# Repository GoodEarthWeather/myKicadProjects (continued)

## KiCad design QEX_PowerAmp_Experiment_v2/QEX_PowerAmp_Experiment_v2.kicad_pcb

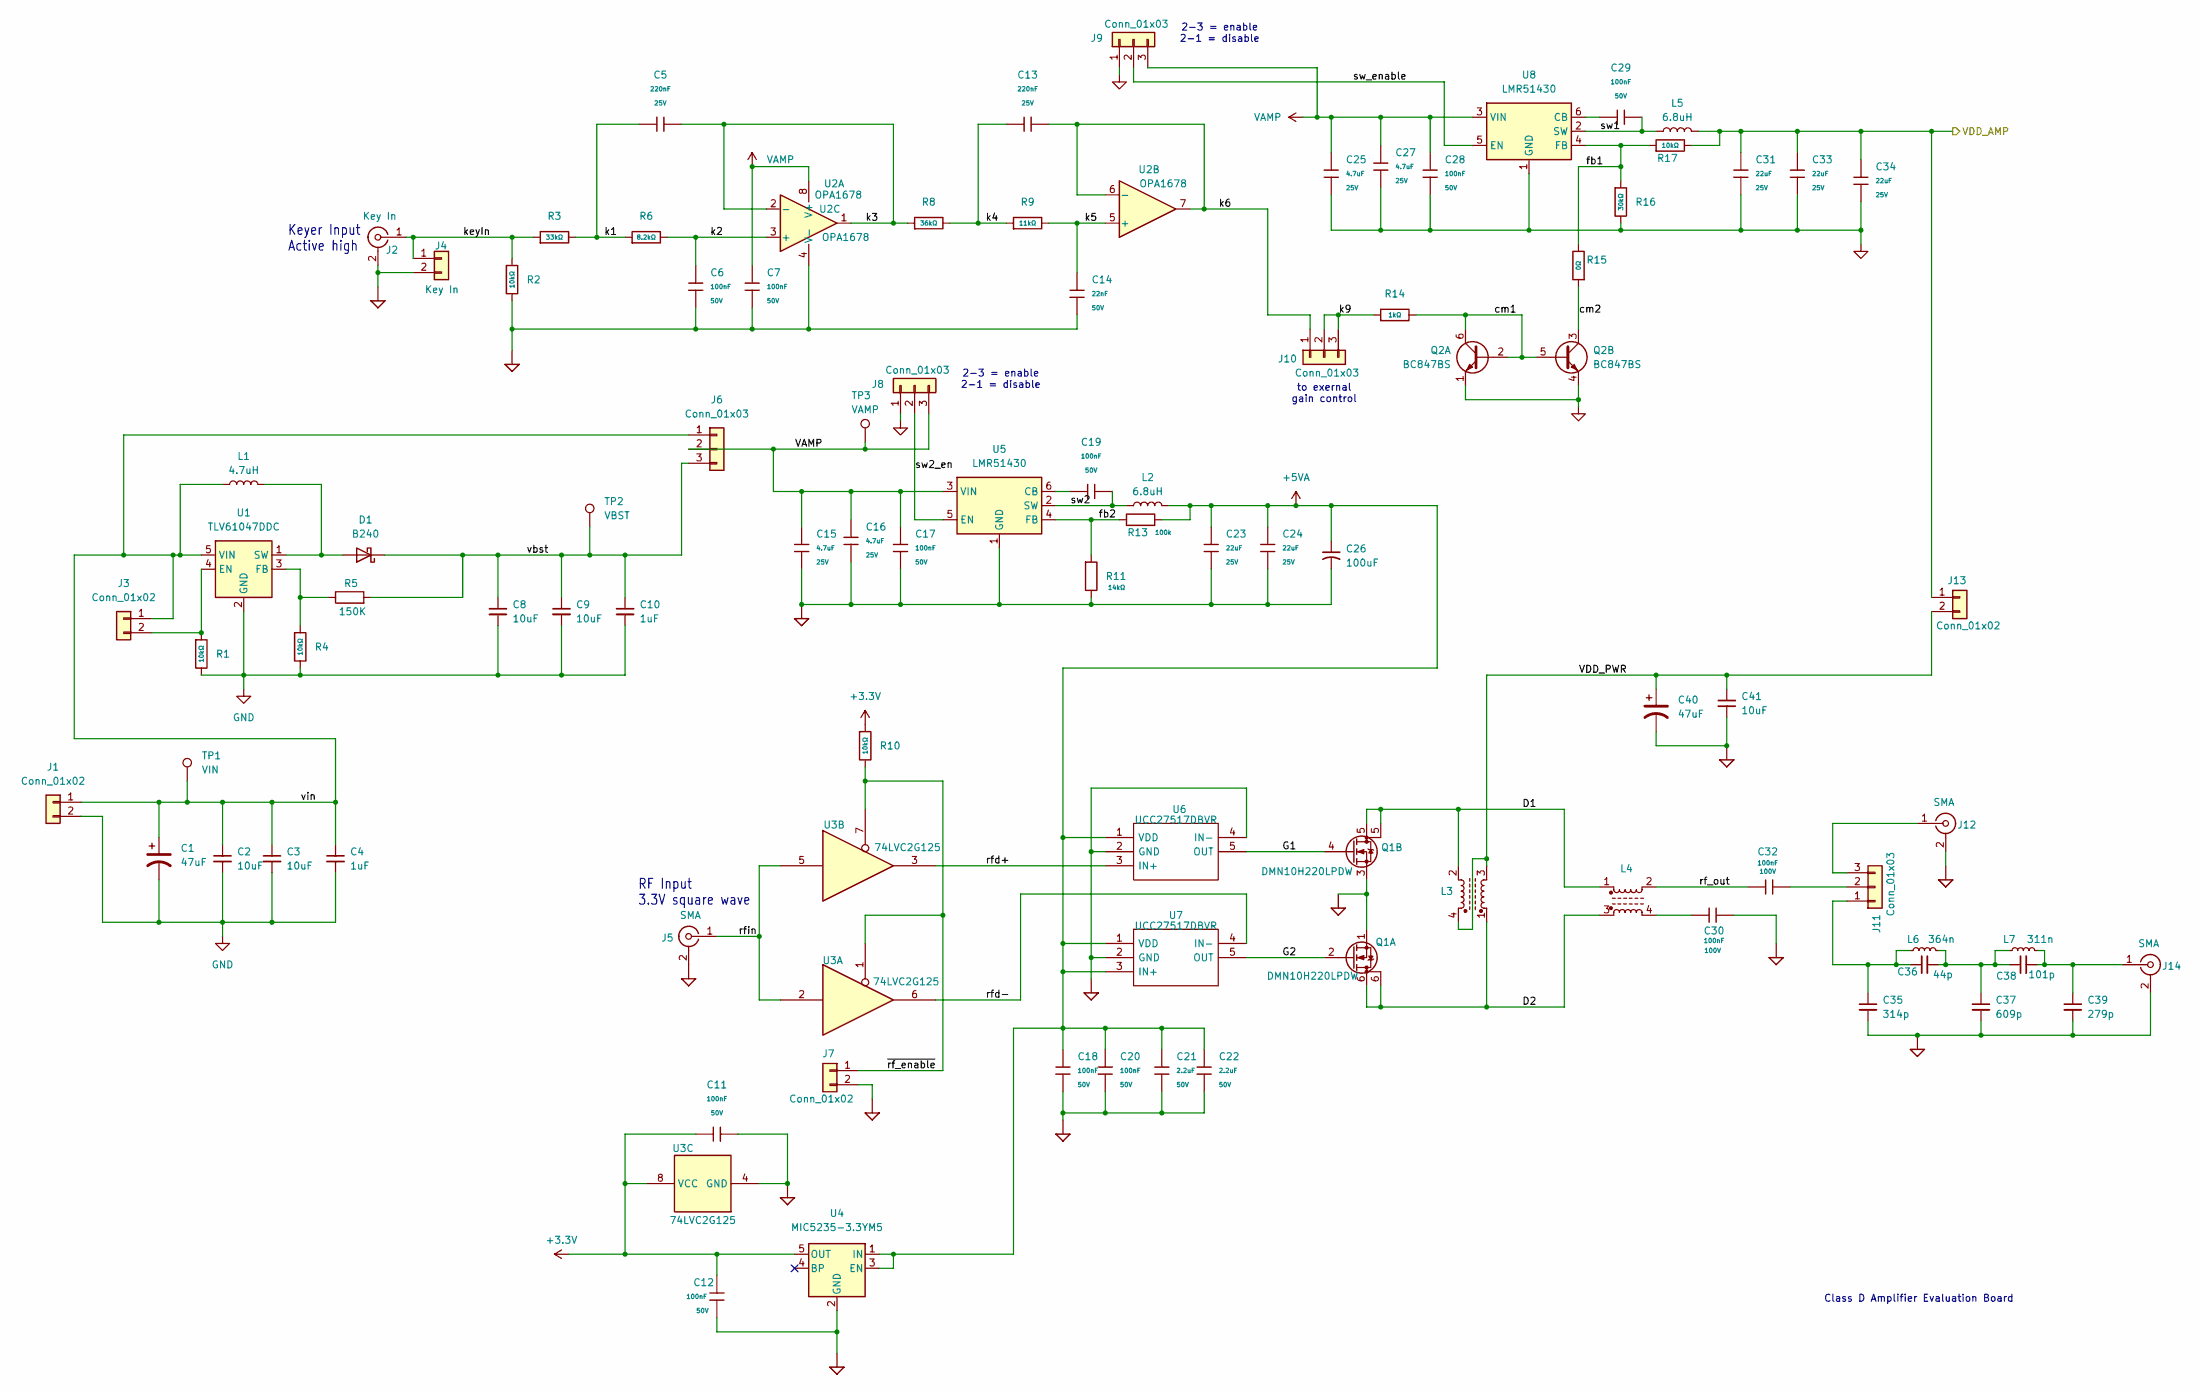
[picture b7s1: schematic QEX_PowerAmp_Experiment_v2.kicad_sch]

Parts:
C1, C40: 47uF; CP_Elec_6.3x5.8; MouserPN 667-EEE-FK1V470P
C2, C3, C8, C9, C41: 10uF; C_1206; MouserPN 810-CGA5L1X7R1H106K1
C4, C10: 1uF; C_0603; MouserPN 963-BASG168AB7105KT
C5, C13: 220nF; C_0603; Voltage Rated 25V; Tolerance ±10%; Part CL10B224KA8NNNC; LCSC C21120
C6, C7, C11, C12, C17, C18, C19, C20, C28, C29: 100nF; C_0603; Voltage Rated 50V; Tolerance ±10%; Part CC0603KRX7R9BB104; LCSC C14663
C14: 22nF; C_0603; Voltage Rated 50V; Tolerance ±10%; Part CL10B223KB8NNNC; LCSC C21122
C15, C16, C25, C27: 4.7uF; C_0805; Voltage Rated 25V; Tolerance ±10%; Part CL21A475KAQNNNE; LCSC C1779
C21, C22: 2.2uF; C_0805; Voltage Rated 50V; Tolerance ±10%; Part CL21A225KBQNNNE; LCSC C377773
C23, C24, C31, C33, C34: 22uF; C_0805; Voltage Rated 25V; Tolerance ±20%; Part CL21A226MAQNNNE; LCSC C45783
C26: 100uF; C_Elec_6.3x5.8; MouserPN 667-EEE-FT1V101AP
C30, C32: 100nF; C_0805; Voltage Rated 100V; Tolerance ±10%; Part CL21B104KCFNNNE; LCSC C28233
C35: 314p; C_1206_3216Metric_Pad1.33x1.80mm_HandSolder
C36: 44p; C_1206_3216Metric_Pad1.33x1.80mm_HandSolder
C37: 609p; C_1206_3216Metric_Pad1.33x1.80mm_HandSolder
C38: 101p; C_1206_3216Metric_Pad1.33x1.80mm_HandSolder
C39: 279p; C_1206_3216Metric_Pad1.33x1.80mm_HandSolder
D1: B240; D_SMB; MouserPN 625-B240A-E3
J1, J3, J7, J13: Conn_01x02; PinHeader_1x02_P2.54mm_Vertical
J2: Key In; SMA_Molex_73251-1153_EdgeMount_Horizontal
J4: Key In; PinHeader_1x02_P2.54mm_Vertical
J5, J12, J14: SMA; SMA_Molex_73251-1153_EdgeMount_Horizontal
J6, J8, J9, J10, J11: Conn_01x03; PinHeader_1x03_P2.54mm_Vertical
L1: 4.7uH; L_TechFuse_SL0420; LCSC C22463808
L2, L5: 6.8uH; L_TechFuse_SL0624; MouserPN 710-7447714068
L3, L4: L_Ferrite_Coupled; Transformer_Toroid_Horizontal_D14.0mm_Amidon-T50
L6: 364n; L_Toroid_Horizontal_D12.7mm_P20.00mm_Diameter14-5mm_Amidon-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
L7: 311n; L_Toroid_Horizontal_D12.7mm_P20.00mm_Diameter14-5mm_Amidon-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
Q1: DMN10H220LPDW; DMN10H220LPDW13; MouserPN 621-DMN10H220LPDW-13
Q2: BC847BS; SOT-363_SC-70-6; Part BC847BS; LCSC C41375126
R1, R2, R4, R10, R17: 10kΩ; R_0603; Overload Voltage (Max) 75V; Tolerance ±1%; Part 0603WAF1002T5E; LCSC C25804
R3: 33kΩ; R_0603; Overload Voltage (Max) 75V; Tolerance ±1%; Part 0603WAF3302T5E; LCSC C4216
R5: 150K; R_0603; JLCPCB C22807
R6: 8.2kΩ; R_0603; Overload Voltage (Max) 75V; Tolerance ±1%; Part 0603WAF8201T5E; LCSC C25981
R8: 36kΩ; R_0603; Overload Voltage (Max) 75V; Tolerance ±1%; Part 0603WAF3602T5E; LCSC C23147
R9: 11kΩ; R_0603; Overload Voltage (Max) 75V; Tolerance ±1%; Part 0603WAF1102T5E; LCSC C25950
R11: 14kΩ; R_0603; Overload Voltage (Max) 75V; Tolerance ±1%; Part 0603WAF3002T5E; LCSC C22984
R13: 100k; R_0603; Overload Voltage (Max) 75V; Tolerance ±1%; Part 0603WAF1002T5E; LCSC C25804
R14: 1kΩ; R_0603; Overload Voltage (Max) 75V; Tolerance ±1%; Part 0603WAF2701T5E; LCSC C21190
R15: 0Ω; R_0603; Overload Voltage (Max) 75V; Tolerance ±1%; Part 0603WAF0000T5E; LCSC C21189
R16: 30kΩ; R_0603; Overload Voltage (Max) 75V; Tolerance ±1%; Part 0603WAF3002T5E; LCSC C22984
TP1: VIN; TestPoint_Keystone_5000-5004_Miniature; MouserPN 534-5003
TP2: VBST; TestPoint_Keystone_5000-5004_Miniature; MouserPN 534-5003
TP3: VAMP; TestPoint_Keystone_5000-5004_Miniature; MouserPN 534-5003
U1: TLV61047DDC; SOT-23-5; MouserPN 595-TLV61047DDCR; JLCPCB C44538408
U2: OPA1678; SOIC-8_3.9x4.9mm_P1.27mm; JLCPCB C192421
U3: 74LVC2G125; SSOP-8_2.95x2.8mm_P0.65mm; MouserPN 595-74LVC2G125DCTRE4
U4: MIC5235-3.3YM5; SOT-23-5; MouserPN 998-MIC5235-3.3YM5TR
U5, U8: LMR51430; SOT-23-6; LCSC C5185863
U6, U7: UCC27517DBVR; SOT-23-5_HandSoldering; Mouser Part Number 595-UCC27517DBVR

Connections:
+3.3V: C11.1, C12.1, R10.1, U3.8 (VCC), U4.5 (OUT)
+5VA: C18.1, C20.1, C21.1, C22.1, C23.1, C24.1, C26.1, L2.2, R13.2, U4.1 (IN), U4.3 (EN), U6.1 (VDD), U7.1 (VDD), U7.3 (IN+)
/D1: L3.2, L4.1, Q1.5 (D)
/D2: L3.1, L4.3, Q1.6 (D)
/G1: Q1.4 (G), U6.5 (OUT)
/G2: Q1.2 (G), U7.5 (OUT)
/VDD_AMP: C31.1, C33.1, C34.1, J13.1, L5.2, R17.2
/VDD_PWR: C40.1, C41.1, J13.2, L3.3, L3.4
/cm1: Q2.2 (B1), Q2.5 (B2), Q2.6 (C1), R14.2
/cm2: Q2.3 (C2), R15.1
/fb1: R15.2, R16.1, R17.1, U8.4 (FB)
/fb2: R11.1, R13.1, U5.4 (FB)
/k1: C5.1, R3.2, R6.1
/k2: C6.1, R6.2, U2.3 (+)
/k3: C5.2, R8.1, U2.1, U2.2 (-)
/k4: C13.1, R8.2, R9.1
/k5: C14.1, R9.2, U2.5 (+)
/k6: C13.2, J10.1, U2.6 (-), U2.7
/k9: J10.2, J10.3, R14.1
/keyIn: J2.1 (In), J4.1, R2.1, R3.1
/rf_out: C32.1, L4.2
/rfd+: U3.3, U6.3 (IN+)
/rfd-: U3.6, U7.4 (IN-)
/rfin: J5.1 (In), U3.2, U3.5
/sw1: C29.2, L5.1, U8.2 (SW)
/sw2: C19.2, L2.1, U5.2 (SW)
/sw2_en: J8.2, U5.5 (EN)
/sw_enable: J9.2, U8.5 (EN)
/vbst: C8.1, C9.1, C10.1, D1.1 (K), J6.3, R5.2, TP2.1
/vin: C1.1, C2.1, C3.1, C4.1, J1.1, J3.1, J6.1, L1.1, TP1.1, U1.5 (VIN)
/~rf_enable: J7.1, R10.2, U3.1, U3.7
GND: C1.2, C2.2, C3.2, C4.2, C6.2, C7.2, C8.2, C9.2, C10.2, C11.2, C12.2, C14.2, C15.2, C16.2, C17.2, C18.2, C20.2, C21.2, C22.2, C23.2, C24.2, C25.2, C26.2, C27.2, C28.2, C30.2, C31.2, C33.2, C34.2, C35.2, C37.2, C39.2, C40.2, C41.2, J1.2, J2.2 (Ext), J4.2, J5.2 (Ext), J7.2, J8.1, J9.1, J12.2 (Ext), J14.2 (Ext), Q1.1 (S), Q1.3 (S), Q2.1 (E1), Q2.4 (E2), R1.2, R2.2, R4.2, R11.2, R16.2, U1.2 (GND), U2.4 (V-), U3.4 (GND), U4.2 (GND), U5.1 (GND), U6.2 (GND), U6.4 (IN-), U7.2 (GND), U8.1 (GND)
unnamed: C30.1, L4.4
unnamed: C36.2, C37.1, C38.1, L6.2, L7.1
unnamed: D1.2 (A), L1.2, U1.1 (SW)
unnamed: J3.2, R1.1, U1.4 (EN)
unnamed: C35.1, C36.1, J11.1, L6.1
unnamed: C32.2, J11.2
unnamed: J11.3, J12.1 (In)
unnamed: C38.2, C39.1, J14.1 (In), L7.2
unnamed: R4.1, R5.1, U1.3 (FB)
unnamed: C19.1, U5.6 (CB)
unnamed: C29.1, U8.6 (CB)
VAMP: C7.1, C15.1, C16.1, C17.1, C25.1, C27.1, C28.1, J6.2, J8.3, J9.3, TP3.1, U2.8 (V+), U5.3 (VIN), U8.3 (VIN)

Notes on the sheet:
to exernal gain control
Class D Amplifier Evaluation Board
RF Input 3.3V square wave
2-3 = enable 2-1 = disable
Keyer Input Active high

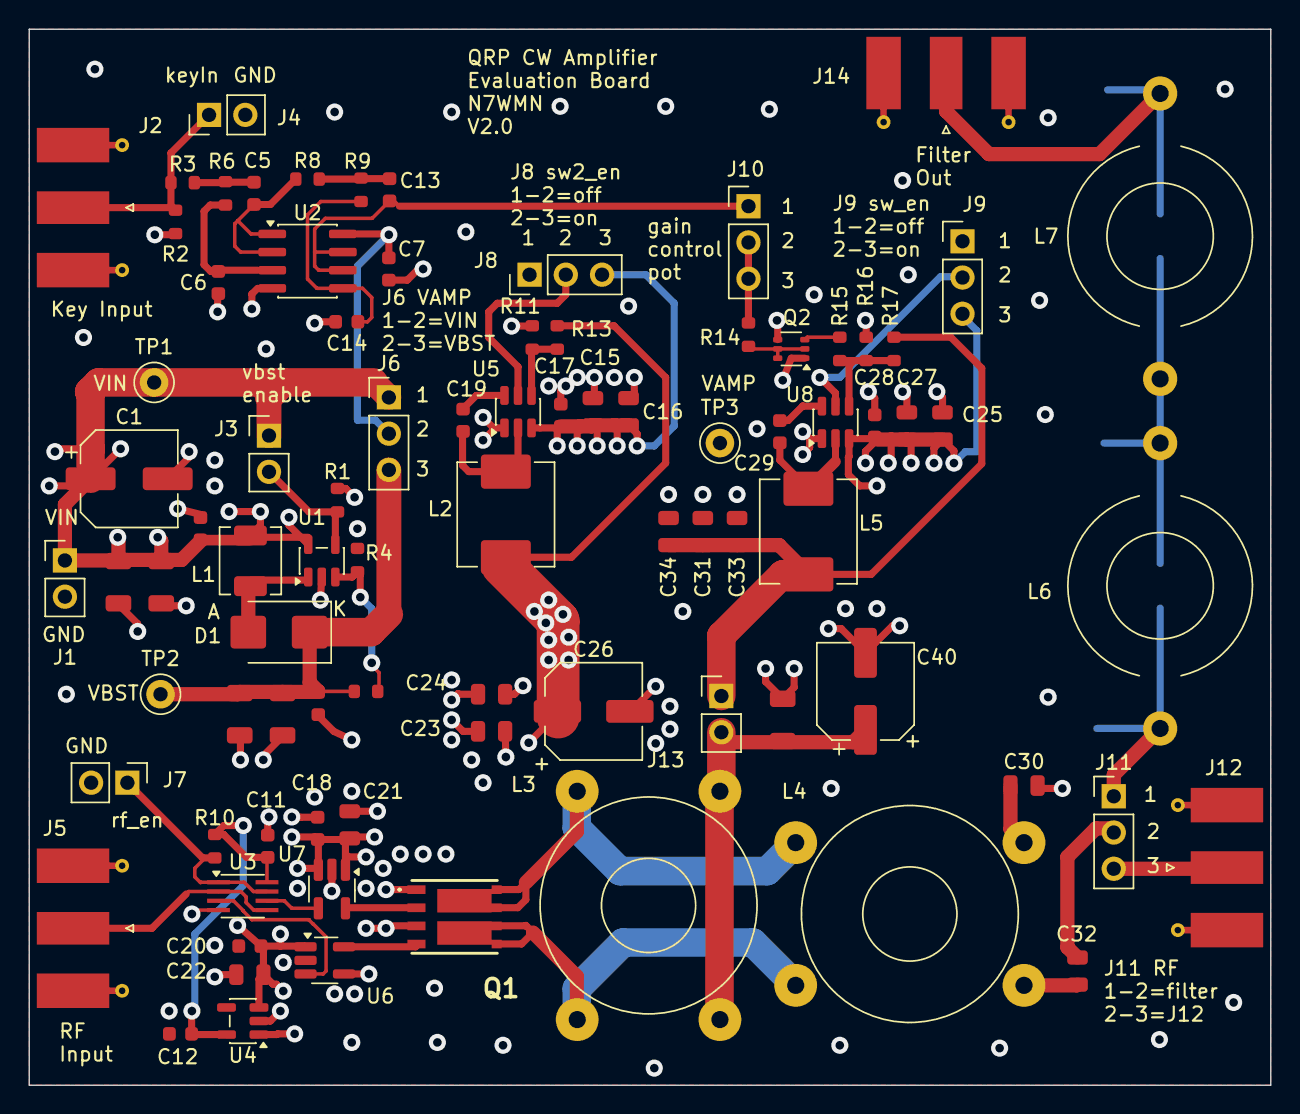
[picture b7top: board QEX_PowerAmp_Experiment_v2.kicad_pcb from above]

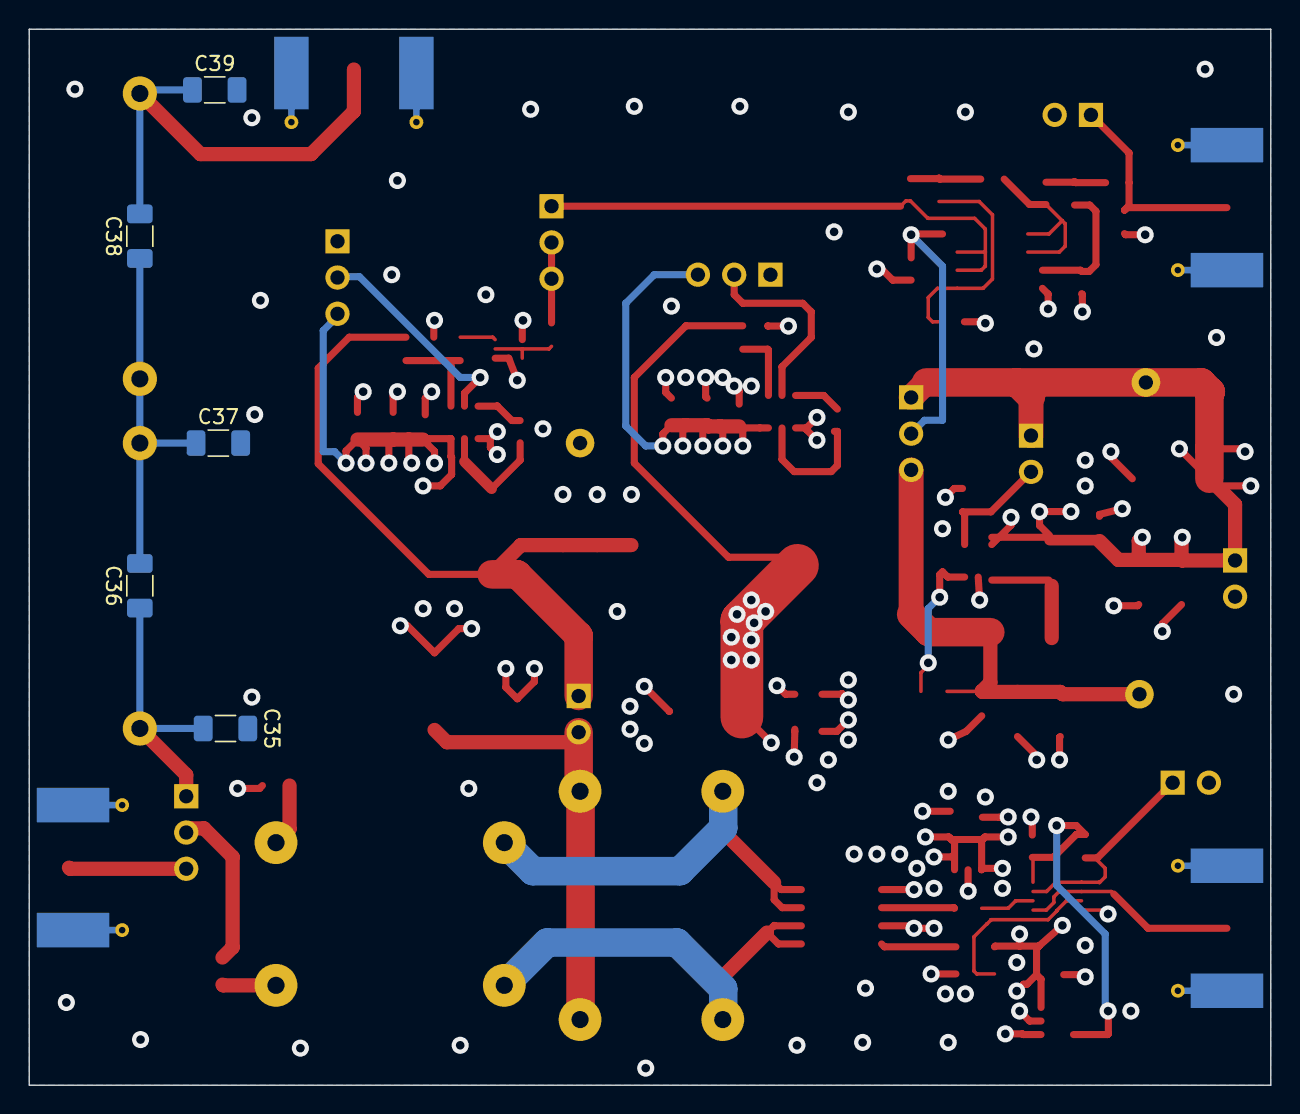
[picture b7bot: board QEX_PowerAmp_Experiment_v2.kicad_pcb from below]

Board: 4 copper layers, 87.0 x 74.0 mm, 91 parts (5 on the bottom side), 44 nets.

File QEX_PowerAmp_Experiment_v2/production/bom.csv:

Designator,Footprint,Comment,LCSC Part #
"C1, C40",CP_Elec_6.3x5.8,47uF,C336786
"C10, C4",C_0603,1uF,C15849
"C11, C12, C17, C18, C19, C20, C28, C29, C6, C7",C_0603,100nF,C14663
"C13, C5",C_0603,220nF,C21120
C14,C_0603,22nF,C21122
"C15, C16, C25, C27",C_0805,4.7uF,C1779
"C2, C3, C41, C8, C9",C_1206,10uF,C13585
"C21, C22",C_0805,2.2uF,C377773
"C23, C24, C31, C33, C34",C_0805,22uF,C45783
C26,C_Elec_6.3x5.8,100uF,C7469933
"C30, C32",C_0805,100nF,C28233
D1,D_SMB,B240,C6807776
L1,L_TechFuse_SL0420,4.7uH,C22463808
"L2, L5",L_TechFuse_SL0624,6.8uH,C22463814
Q1,DMN10H220LPDW13,DMN10H220LPDW,
Q2,SOT-363_SC-70-6,BC847BS,C41375126
"R1, R10, R13, R17, R2, R4",R_0603,10kΩ,C25804
"R11, R16",R_0603,30kΩ,C22984
R14,R_0603,1kΩ,C13167
R15,R_0603,0Ω,C21189
R3,R_0603,33kΩ,C4216
R5,R_0603,150K,C22807
R6,R_0603,8.2kΩ,C25981
R8,R_0603,36kΩ,C23147
R9,R_0603,11kΩ,C25950
U1,SOT-23-5,TLV61047DDC,C44538408
U2,SOIC-8_3.9x4.9mm_P1.27mm,OPA1678,C192421
U3,SSOP-8_2.95x2.8mm_P0.65mm,74LVC2G125,C2675807
U4,SOT-23-5,MIC5235-3.3YM5,C7202997
"U5, U8",SOT-23-6,LMR51430,C5185863
"U6, U7",SOT-23-5_HandSoldering,UCC27517DBVR,C99395
